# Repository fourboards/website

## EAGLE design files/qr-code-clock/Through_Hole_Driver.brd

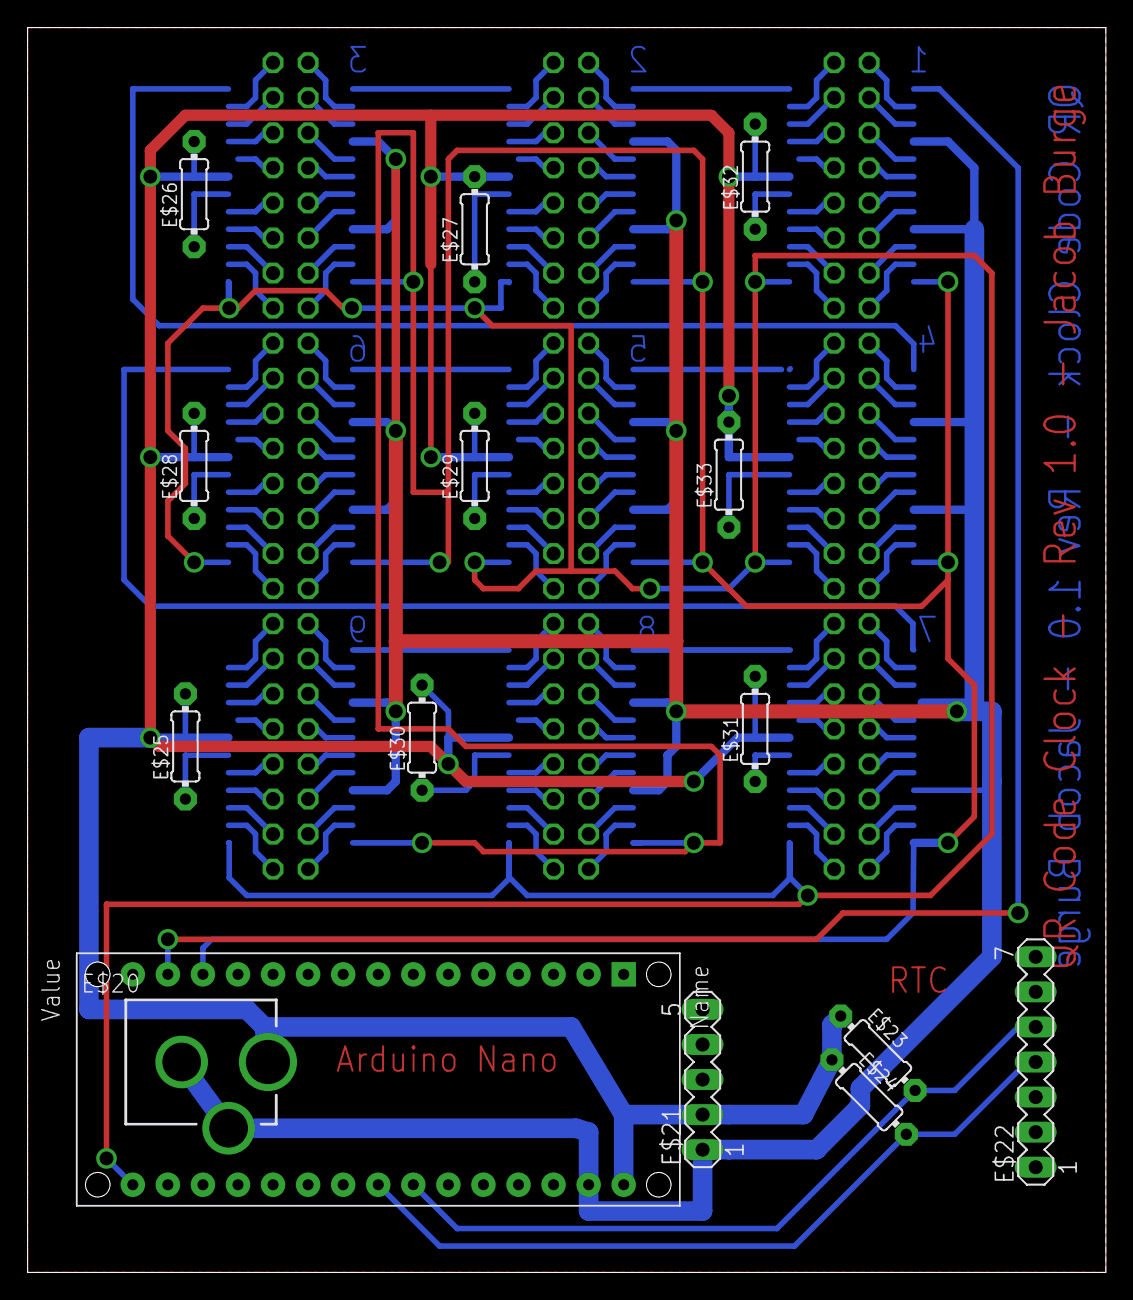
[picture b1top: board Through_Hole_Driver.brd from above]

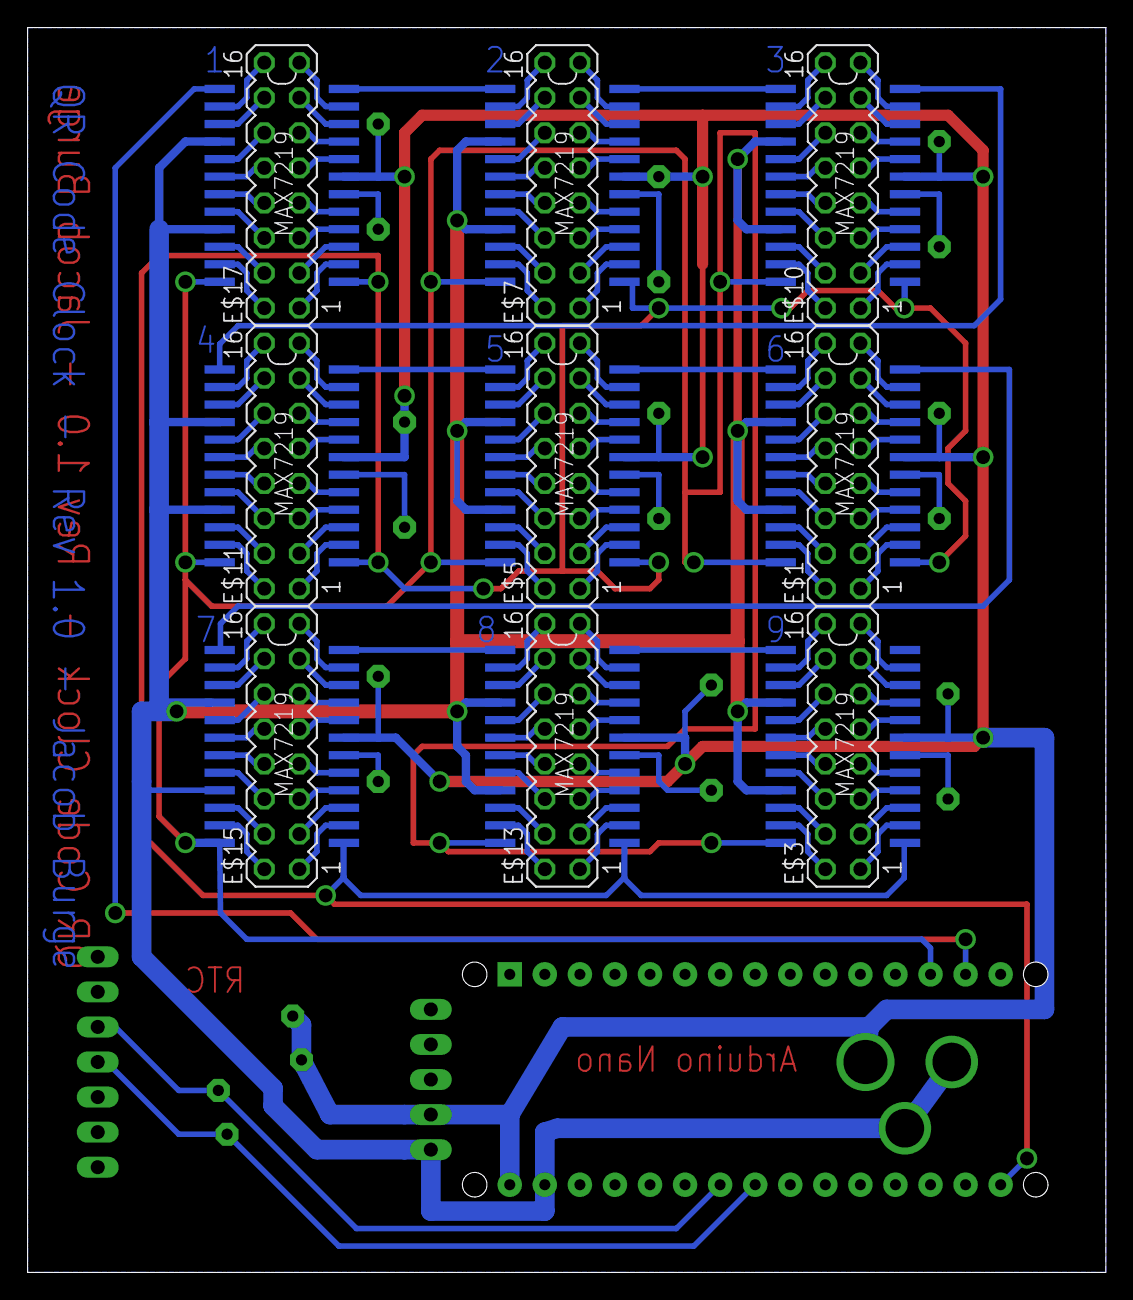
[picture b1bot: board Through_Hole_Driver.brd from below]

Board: 2 copper layers, 78.1 x 90.2 mm, 33 parts (18 on the bottom side), 166 nets.

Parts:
E$1, E$3, E$5, E$7, E$10, E$11, E$13, E$15, E$17: MA08-2
E$2, E$4, E$6, E$8, E$9, E$12, E$14, E$16, E$18: MAX7219
E$19: PDIP-32
E$20: DCJACK_2MM_PTH
E$21: MA05-1
E$22: MA07-1
E$23, E$24, E$25, E$26, E$27, E$28, E$29, E$30, E$31, E$32, E$33: 0204/7

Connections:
S$1: E$9.23, E$10.15
S$4: E$9.22, E$10.13
S$5: E$9.21, E$10.11
S$6: E$9.20, E$10.9
S$7: E$9.17, E$10.7
S$9: E$9.16, E$10.5
S$10: E$9.15, E$10.3
S$11: E$9.14, E$10.1
S$12: E$9.2, E$10.16
S$13: E$9.3, E$10.14
S$14: E$9.5, E$10.12
S$15: E$9.6, E$10.10
S$16: E$9.7, E$10.8
S$17: E$9.8, E$10.6
S$18: E$9.10, E$10.4
S$19: E$9.11, E$10.2
S$20: E$1.15, E$2.23
S$21: E$1.13, E$2.22
S$22: E$1.11, E$2.21
S$23: E$1.9, E$2.20
S$25: E$1.7, E$2.17
S$26: E$1.5, E$2.16
S$27: E$1.3, E$2.15
S$28: E$1.1, E$2.14
S$29: E$1.16, E$2.2
S$30: E$1.14, E$2.3
S$31: E$1.12, E$2.5
S$32: E$1.10, E$2.6
S$33: E$1.8, E$2.7
S$34: E$1.6, E$2.8
S$35: E$1.4, E$2.10
S$36: E$1.2, E$2.11
S$37: E$3.15, E$4.23
S$38: E$3.13, E$4.22
S$39: E$3.11, E$4.21
S$40: E$3.9, E$4.20
S$43: E$3.7, E$4.17
S$44: E$3.5, E$4.16
S$45: E$3.3, E$4.15
S$46: E$3.1, E$4.14
S$47: E$3.16, E$4.2
S$48: E$3.14, E$4.3
S$49: E$3.12, E$4.5
S$50: E$3.10, E$4.6
S$51: E$3.8, E$4.7
S$52: E$3.6, E$4.8
S$53: E$3.4, E$4.10
S$54: E$3.2, E$4.11
S$55: E$5.15, E$6.23
S$57: E$5.13, E$6.22
S$58: E$5.11, E$6.21
S$59: E$5.9, E$6.20
S$60: E$5.7, E$6.17
S$61: E$5.5, E$6.16
S$62: E$5.3, E$6.15
S$63: E$5.1, E$6.14
S$64: E$5.16, E$6.2
S$65: E$5.14, E$6.3
S$66: E$5.12, E$6.5
S$68: E$5.10, E$6.6
S$69: E$5.8, E$6.7
S$70: E$5.6, E$6.8
S$71: E$5.4, E$6.10
S$72: E$5.2, E$6.11
S$73: E$7.15, E$8.23
S$74: E$7.13, E$8.22
S$75: E$7.11, E$8.21
S$76: E$7.9, E$8.20
S$77: E$7.7, E$8.17
S$78: E$7.5, E$8.16
S$79: E$7.3, E$8.15
S$80: E$7.1, E$8.14
S$81: E$7.16, E$8.2
S$82: E$7.14, E$8.3
S$83: E$7.12, E$8.5
S$84: E$7.10, E$8.6
S$85: E$7.8, E$8.7
S$86: E$7.6, E$8.8
S$87: E$7.4, E$8.10
S$88: E$7.2, E$8.11
S$89: E$13.15, E$14.23
S$90: E$13.13, E$14.22
S$91: E$13.11, E$14.21
S$92: E$13.9, E$14.20
S$93: E$13.7, E$14.17
S$94: E$13.5, E$14.16
S$95: E$13.3, E$14.15
S$96: E$13.1, E$14.14
S$97: E$13.16, E$14.2
S$98: E$13.14, E$14.3
S$99: E$13.12, E$14.5
S$100: E$13.10, E$14.6
S$101: E$13.8, E$14.7
S$102: E$13.6, E$14.8
S$103: E$13.4, E$14.10
S$104: E$13.2, E$14.11
S$105: E$15.15, E$16.23
S$106: E$15.13, E$16.22
S$107: E$15.11, E$16.21
S$108: E$15.9, E$16.20
S$109: E$15.7, E$16.17
S$110: E$15.5, E$16.16
S$111: E$15.3, E$16.15
S$112: E$15.1, E$16.14
S$113: E$15.16, E$16.2
S$114: E$15.14, E$16.3
S$115: E$15.12, E$16.5
S$116: E$15.10, E$16.6
S$117: E$15.8, E$16.7
S$118: E$15.6, E$16.8
S$119: E$15.4, E$16.10
S$120: E$15.2, E$16.11
S$121: E$11.15, E$12.23
S$122: E$11.13, E$12.22
S$123: E$11.11, E$12.21
S$124: E$11.9, E$12.20
S$125: E$11.7, E$12.17
S$126: E$11.5, E$12.16
S$127: E$11.3, E$12.15
S$128: E$11.1, E$12.14
S$129: E$11.16, E$12.2
S$130: E$11.14, E$12.3
S$131: E$11.12, E$12.5
S$132: E$11.10, E$12.6
S$133: E$11.8, E$12.7
S$134: E$11.6, E$12.8
S$135: E$11.4, E$12.10
S$136: E$11.2, E$12.11
S$137: E$17.15, E$18.23
S$138: E$17.13, E$18.22
S$139: E$17.11, E$18.21
S$140: E$17.9, E$18.20
S$141: E$17.7, E$18.17
S$142: E$17.5, E$18.16
S$143: E$17.3, E$18.15
S$144: E$17.1, E$18.14
S$145: E$17.16, E$18.2
S$146: E$17.14, E$18.3
S$147: E$17.12, E$18.5
S$148: E$17.10, E$18.6
S$149: E$17.8, E$18.7
S$150: E$17.6, E$18.8
S$151: E$17.4, E$18.10
S$153: E$17.2, E$18.11
S$154: E$2.13, E$4.13, E$6.13, E$8.13, E$9.13, E$12.13, E$14.13, E$16.13, E$18.13, E$19.D13
S$155: E$18.1, E$19.D11
S$157: E$2.12, E$4.12, E$6.12, E$8.12, E$9.12, E$12.12, E$14.12, E$16.12, E$18.12, E$19.D10
S$158: E$8.1, E$18.24
S$159: E$8.24, E$9.1
S$160: E$9.24, E$12.1
S$162: E$2.1, E$6.24
S$163: E$2.24, E$16.1
S$164: E$4.1, E$14.24
S$166: E$2.19, E$4.19, E$6.19, E$8.19, E$9.19, E$12.19, E$14.19, E$16.19, E$18.19, E$19.VIN, E$20.PWR, E$23.1, E$24.1, E$25.2, E$26.2, E$28.2, E$29.2, E$30.2, E$31.2, E$32.2
S$167: E$19.A2, E$22.5, E$23.2
S$168: E$2.4, E$2.9, E$4.4, E$4.9, E$6.4, E$6.9, E$8.4, E$8.9, E$9.4, E$9.9, E$12.4, E$12.9, E$14.4, E$14.9, E$16.4, E$16.9, E$18.4, E$18.9, E$19.GND1, E$20.GND, E$20.GNDBREAK
S$169: E$19.A3, E$22.4, E$24.2
S$170: E$9.18, E$26.1
S$171: E$8.18, E$27.1
S$172: E$4.18, E$25.1
S$173: E$2.18, E$28.1
S$174: E$6.18, E$29.1
S$175: E$14.18, E$30.1
S$176: E$16.18, E$31.1
S$177: E$18.18, E$32.1
S$178: E$12.18, E$33.1
